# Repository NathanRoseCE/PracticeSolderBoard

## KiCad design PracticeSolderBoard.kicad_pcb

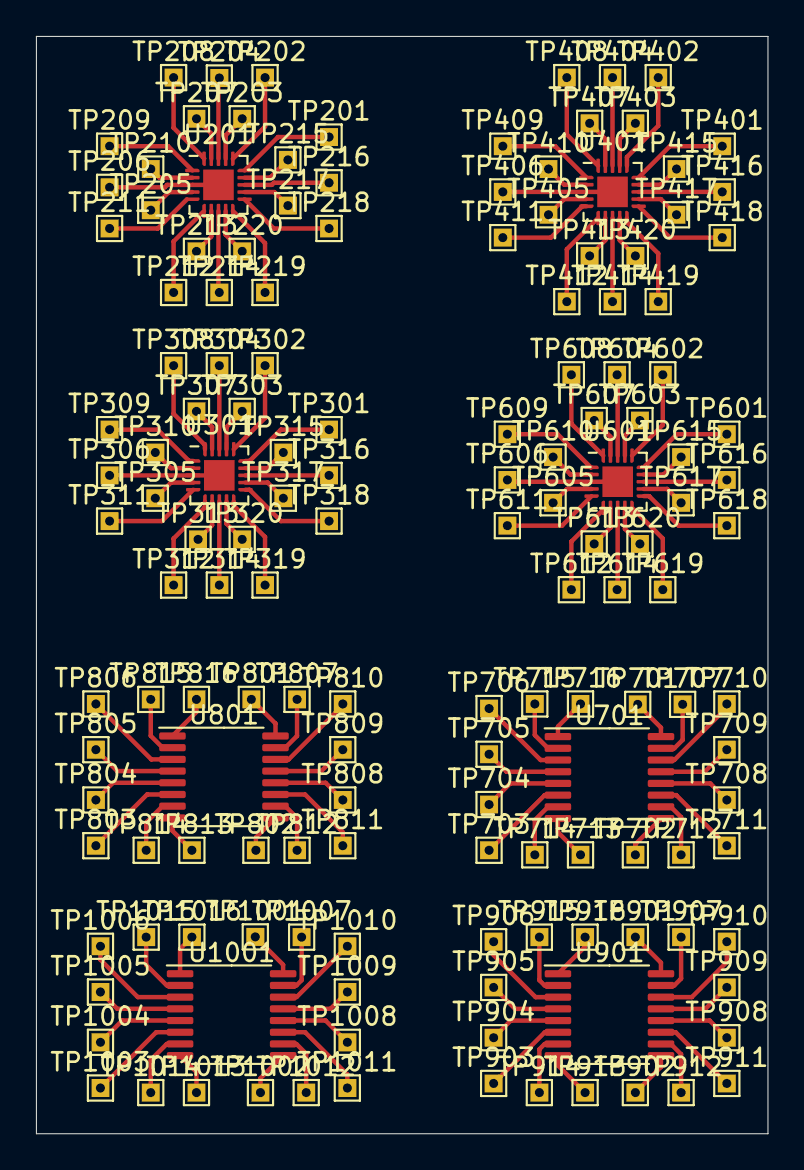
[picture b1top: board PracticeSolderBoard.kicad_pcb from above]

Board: 2 copper layers, 40.6 x 61.0 mm, 152 parts (0 on the bottom side), 144 nets.

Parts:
TP201, TP202, TP203, TP204, TP205, TP206, TP207, TP208, TP209, TP210, TP211, TP212, TP213, TP214, TP215, TP216, TP217, TP218, TP219, TP220, TP301, TP302, TP303, TP304, TP305, TP306, TP307, TP308, TP309, TP310, TP311, TP312, TP313, TP314, TP315, TP316, TP317, TP318, TP319, TP320, TP401, TP402, TP403, TP404, TP405, TP406, TP407, TP408, TP409, TP410, TP411, TP412, TP413, TP414, TP415, TP416, TP417, TP418, TP419, TP420, TP601, TP602, TP603, TP604, TP605, TP606, TP607, TP608, TP609, TP610, TP611, TP612, TP613, TP614, TP615, TP616, TP617, TP618, TP619, TP620, TP701, TP702, TP703, TP704, TP705, TP706, TP707, TP708, TP709, TP710, TP711, TP712, TP713, TP714, TP715, TP716, TP801, TP802, TP803, TP804, TP805, TP806, TP807, TP808, TP809, TP810, TP811, TP812, TP813, TP814, TP815, TP816, TP901, TP902, TP903, TP904, TP905, TP906, TP907, TP908, TP909, TP910, TP911, TP912, TP913, TP914, TP915, TP916, TP1001, TP1002, TP1003, TP1004, TP1005, TP1006, TP1007, TP1008, TP1009, TP1010, TP1011, TP1012, TP1013, TP1014, TP1015, TP1016: TestPoint; TestPoint_THTPad_1.0x1.0mm_Drill0.5mm
U201, U301, U401, U601: ATtiny816-M; VQFN-20-1EP_3x3mm_P0.4mm_EP1.7x1.7mm
U701, U801, U901, U1001: LPC811M001JDH16; TSSOP-16_4.4x5mm_P0.65mm

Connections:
unnamed: TP201.1, U201.15
unnamed: TP202.1, U201.16
unnamed: TP203.1, U201.17
unnamed: TP204.1, U201.18
unnamed: TP205.1, U201.4
unnamed: TP206.1, U201.3, U201.21
unnamed: TP207.1, U201.19
unnamed: TP208.1, U201.20
unnamed: TP209.1, U201.1
unnamed: TP210.1, U201.2
unnamed: TP211.1, U201.5
unnamed: TP212.1, U201.6
unnamed: TP213.1, U201.7
unnamed: TP214.1, U201.8
unnamed: TP215.1, U201.14
unnamed: TP216.1, U201.13
unnamed: TP217.1, U201.12
unnamed: TP218.1, U201.11
unnamed: TP219.1, U201.10
unnamed: TP220.1, U201.9
unnamed: TP301.1, U301.15
unnamed: TP302.1, U301.16
unnamed: TP303.1, U301.17
unnamed: TP304.1, U301.18
unnamed: TP305.1, U301.4
unnamed: TP306.1, U301.3, U301.21
unnamed: TP307.1, U301.19
unnamed: TP308.1, U301.20
unnamed: TP309.1, U301.1
unnamed: TP310.1, U301.2
unnamed: TP311.1, U301.5
unnamed: TP312.1, U301.6
unnamed: TP313.1, U301.7
unnamed: TP314.1, U301.8
unnamed: TP315.1, U301.14
unnamed: TP316.1, U301.13
unnamed: TP317.1, U301.12
unnamed: TP318.1, U301.11
unnamed: TP319.1, U301.10
unnamed: TP320.1, U301.9
unnamed: TP401.1, U401.15
unnamed: TP402.1, U401.16
unnamed: TP403.1, U401.17
unnamed: TP404.1, U401.18
unnamed: TP405.1, U401.4
unnamed: TP406.1, U401.3, U401.21
unnamed: TP407.1, U401.19
unnamed: TP408.1, U401.20
unnamed: TP409.1, U401.1
unnamed: TP410.1, U401.2
unnamed: TP411.1, U401.5
unnamed: TP412.1, U401.6
unnamed: TP413.1, U401.7
unnamed: TP414.1, U401.8
unnamed: TP415.1, U401.14
unnamed: TP416.1, U401.13
unnamed: TP417.1, U401.12
unnamed: TP418.1, U401.11
unnamed: TP419.1, U401.10
unnamed: TP420.1, U401.9
unnamed: TP601.1, U601.15
unnamed: TP602.1, U601.16
unnamed: TP603.1, U601.17
unnamed: TP604.1, U601.18
unnamed: TP605.1, U601.4
unnamed: TP606.1, U601.3, U601.21
unnamed: TP607.1, U601.19
unnamed: TP608.1, U601.20
unnamed: TP609.1, U601.1
unnamed: TP610.1, U601.2
unnamed: TP611.1, U601.5
unnamed: TP612.1, U601.6
unnamed: TP613.1, U601.7
unnamed: TP614.1, U601.8
unnamed: TP615.1, U601.14
unnamed: TP616.1, U601.13
unnamed: TP617.1, U601.12
unnamed: TP618.1, U601.11
unnamed: TP619.1, U601.10
unnamed: TP620.1, U601.9
unnamed: TP701.1, U701.16
unnamed: TP702.1, U701.9
unnamed: TP703.1, U701.6
unnamed: TP704.1, U701.5
unnamed: TP705.1, U701.4
unnamed: TP706.1, U701.3
unnamed: TP707.1, U701.15
unnamed: TP708.1, U701.12
unnamed: TP709.1, U701.13
unnamed: TP710.1, U701.14
unnamed: TP711.1, U701.11
unnamed: TP712.1, U701.10
unnamed: TP713.1, U701.8
unnamed: TP714.1, U701.7
unnamed: TP715.1, U701.2
unnamed: TP716.1, U701.1
unnamed: TP801.1, U801.16
unnamed: TP802.1, U801.9
unnamed: TP803.1, U801.6
unnamed: TP804.1, U801.5
unnamed: TP805.1, U801.4
unnamed: TP806.1, U801.3
unnamed: TP807.1, U801.15
unnamed: TP808.1, U801.12
unnamed: TP809.1, U801.13
unnamed: TP810.1, U801.14
unnamed: TP811.1, U801.11
unnamed: TP812.1, U801.10
unnamed: TP813.1, U801.8
unnamed: TP814.1, U801.7
unnamed: TP815.1, U801.2
unnamed: TP816.1, U801.1
unnamed: TP901.1, U901.16
unnamed: TP902.1, U901.9
unnamed: TP903.1, U901.6
unnamed: TP904.1, U901.5
unnamed: TP905.1, U901.4
unnamed: TP906.1, U901.3
unnamed: TP907.1, U901.15
unnamed: TP908.1, U901.12
unnamed: TP909.1, U901.13
unnamed: TP910.1, U901.14
unnamed: TP911.1, U901.11
unnamed: TP912.1, U901.10
unnamed: TP913.1, U901.8
unnamed: TP914.1, U901.7
unnamed: TP915.1, U901.2
unnamed: TP916.1, U901.1
unnamed: TP1001.1, U1001.16
unnamed: TP1002.1, U1001.9
unnamed: TP1003.1, U1001.6
unnamed: TP1004.1, U1001.5
unnamed: TP1005.1, U1001.4
unnamed: TP1006.1, U1001.3
unnamed: TP1007.1, U1001.15
unnamed: TP1008.1, U1001.12
unnamed: TP1009.1, U1001.13
unnamed: TP1010.1, U1001.14
unnamed: TP1011.1, U1001.11
unnamed: TP1012.1, U1001.10
unnamed: TP1013.1, U1001.8
unnamed: TP1014.1, U1001.7
unnamed: TP1015.1, U1001.2
unnamed: TP1016.1, U1001.1

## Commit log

2020-07-26 Done
